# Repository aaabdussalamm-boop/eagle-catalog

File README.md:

# 🔌 Eagle Catalog

Koleksi desain PCB untuk aplikasi **Biomedical, Audio, dan Power Supply** menggunakan Autodesk Eagle.

🌐 **Website:** https://aaabdussalamm-boop.github.io/eagle-catalog/

---

## 📂 Daftar Proyek

### ⚕️ Biomedical Electronics

#### 1. **Holter AD - 2 Channel ECG Monitor**
Holter monitor untuk monitoring ECG jangka panjang dengan ESP32 DevKit V1.
- **IC Utama:** 2x AD620, TL084
- **MCU:** ESP32 DevKit V1
- **Fitur:** Dual channel, WiFi/Bluetooth
- **Files:** [`HOLTER AD.sch`](HOLTER%20AD.sch) | [`HOLTER AD.brd`](HOLTER%20AD.brd)

#### 2. **ECG Circuit**
Rangkaian elektrokardiogram single channel dengan DRL circuit.
- **IC Utama:** AD620, TL084, OP07
- **Fitur:** DRL (Driven Right Leg) circuit
- **Files:** [`ecg.sch`](ecg.sch) | [`ecg.brd`](ecg.brd)

---

### 🎵 Audio Electronics

#### 3. **PCG Quad - Preamp & Filter**
Preamp dan filter audio 4-channel menggunakan TL084 dengan built-in voltage inverter.
- **IC Utama:** TL084 (Quad Op-Amp)
- **Power:** Built-in IC 7660 inverter
- **Supply:** ±12V atau ±15V
- **Files:** [`pcg_quad.sch`](pcg_quad.sch) | [`pcg_quad.brd`](pcg_quad.brd)

---

### ⚡ Power Supply

#### 4. **IC 7660 - Voltage Inverter**
Rangkaian pembuat tegangan negatif untuk dual supply op-amp.
- **IC Utama:** ICL7660
- **Input:** +5V hingga +12V DC
- **Output:** -5V hingga -12V DC
- **Arus Max:** 100mA
- **Files:** [`7660.sch`](7660.sch) | [`7660.brd`](7660.brd)

---

## 🚀 Cara Menggunakan

### 1. **Clone Repository**
```bash
git clone https://github.com/aaabdussalamm-boop/eagle-catalog.git
cd eagle-catalog
```

### 2. **Buka di Eagle**
- Download Autodesk Eagle (versi gratis tersedia)
- Buka file `.sch` untuk melihat schematic
- Buka file `.brd` untuk melihat board layout

### 3. **Edit & Customize**
- Modifikasi sesuai kebutuhan Anda
- Jalankan DRC (Design Rule Check)
- Export ke Gerber untuk produksi PCB

---

## 🤝 Kontribusi

**Kami menerima kontribusi dari siapa saja!** 🎉

Apakah Anda punya desain PCB yang ingin dibagikan? Ikuti langkah mudah ini:

### Quick Start:
1. **Fork** repository ini
2. **Upload** file .sch dan .brd Anda
3. **Create Pull Request**
4. Tunggu review (1-3 hari)

📖 **Panduan Lengkap:** Baca [CONTRIBUTING.md](CONTRIBUTING.md) untuk tutorial detail dengan screenshot.

### Yang Bisa Dikontribusikan:
- ✅ Schematic Eagle (.sch)
- ✅ Board layout Eagle (.brd)
- ✅ Custom libraries (.lbr)
- ✅ Preview/screenshot (.png, .jpg)
- ✅ Dokumentasi

---

## 📁 Struktur Folder

```
eagle-catalog/
├── projects/
│   ├── biomedical/       # Proyek biomedical
│   ├── audio/            # Proyek audio
│   ├── power-supply/     # Power supply
│   ├── iot-embedded/     # IoT & embedded
│   └── others/           # Kategori lainnya
├── libraries/            # Custom libraries
├── index.html            # Website
└── README.md
```

---

## 🛠️ Software yang Digunakan

- **Autodesk Eagle** - PCB design software
  - Download: https://www.autodesk.com/products/eagle/free-download
  - Versi gratis tersedia untuk hobbyist

---

## 📚 Resources

### Tutorial Eagle:
- [Eagle Tutorial - Sparkfun](https://learn.sparkfun.com/tutorials/using-eagle-schematic)
- [Eagle Documentation - Autodesk](https://www.autodesk.com/products/eagle/learn)

### Untuk Biomedical Projects:
- ⚠️ **PENTING:** Rangkaian biomedical dalam repository ini untuk tujuan pembelajaran dan penelitian saja
- Tidak boleh digunakan untuk diagnosis medis tanpa sertifikasi yang sesuai
- Selalu gunakan isolated power supply untuk keamanan pasien

### PCB Manufacturing:
- [JLCPCB](https://jlcpcb.com/)
- [PCBWay](https://www.pcbway.com/)
- [OSH Park](https://oshpark.com/)

---

## 🐛 Melaporkan Issue

Menemukan bug atau ada saran? Silakan buat [Issue](https://github.com/aaabdussalamm-boop/eagle-catalog/issues) dengan detail yang jelas.

---

## 📜 Lisensi

Repository ini dilisensikan di bawah [MIT License](LICENSE) - silakan gunakan, modifikasi, dan distribusikan dengan bebas.

Dengan berkontribusi ke repository ini, Anda setuju kontribusi Anda juga akan dilisensikan di bawah MIT License.

---

## 🌟 Contributors

Terima kasih kepada semua yang telah berkontribusi! ❤️

<!-- ALL-CONTRIBUTORS-LIST:START -->
<!-- Kontributor akan ditambahkan di sini -->
<!-- ALL-CONTRIBUTORS-LIST:END -->

---

## 💬 Kontak

- **GitHub:** [@aaabdussalamm-boop](https://github.com/aaabdussalamm-boop)
- **Website:** https://aaabdussalamm-boop.github.io/eagle-catalog/
- **Issues:** [Create New Issue](https://github.com/aaabdussalamm-boop/eagle-catalog/issues/new)

---

## 🙏 Acknowledgments

- Komunitas elektronika Indonesia
- Autodesk Eagle Community
- Semua kontributor open source

---

**⭐ Jangan lupa beri star jika repository ini bermanfaat!**

Made with ❤️ for the electronics community

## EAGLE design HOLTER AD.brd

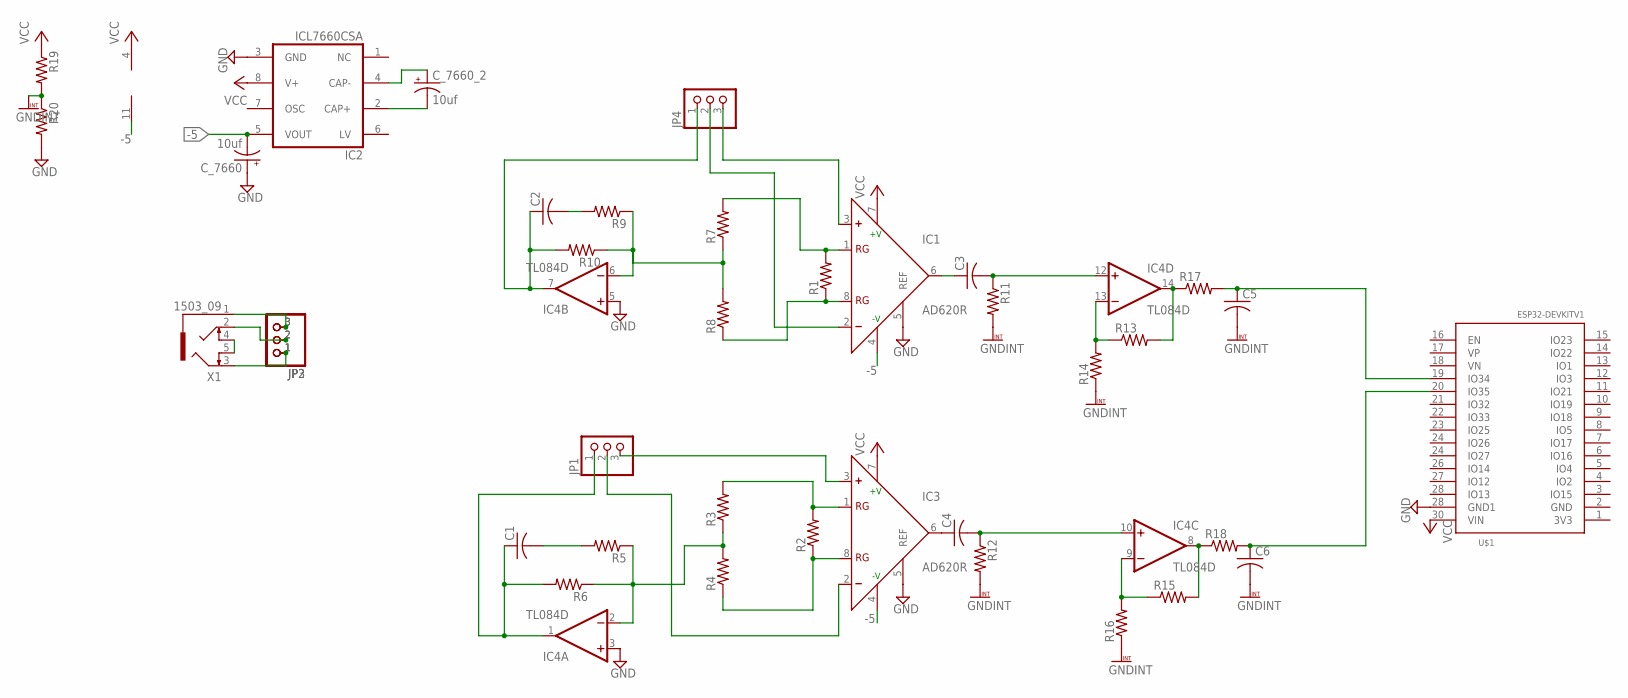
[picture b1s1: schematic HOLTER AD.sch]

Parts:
C1, C2, C3, C4, C5, C6: C-US050-030X075; C050-030X075
C_7660, C_7660_2: 10uf; E2-5
IC1, IC3: AD620R; SO8
IC2: ICL7660CSA; SO08
IC4: TL084D; SO14
JP1, JP2, JP3, JP4: PINHD-1X3; 1X03
R1, R2, R3, R4, R5, R6, R7, R8, R9, R10, R11, R12, R13, R14, R15, R16, R17, R18, R19, R20: R-US_0207/10; 0207/10
U$1: ESP32DEVKITV1; ESP32-DEVKITV1
X1: 1503_09

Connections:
-5: C_7660.-, IC1.4 (-V), IC2.5 (VOUT), IC3.4 (-V), IC4.11 (V-)
GND: C_7660.+, IC1.5 (REF), IC2.3 (GND), IC3.5 (REF), IC4.3 (+IN), IC4.5 (+IN), R20.2, U$1.28 (IO13)
GNDINT: C5.2, C6.2, R11.2, R12.2, R14.1, R16.1, R19.2, R20.1
unnamed: X1.4, X1.5
unnamed: C_7660_2.+, IC2.4 (CAP-)
unnamed: IC1.1 (RG), R1.2, R7.2
unnamed: IC1.8 (RG), R1.1, R8.1
unnamed: IC3.1 (RG), R2.2, R3.2
unnamed: C_7660_2.-, IC2.2 (CAP+)
unnamed: IC3.8 (RG), R2.1, R4.1
unnamed: IC1.3 (+), JP4.3
unnamed: IC1.2 (-), JP4.2
unnamed: IC4.2 (-IN), R3.1, R4.2, R5.1, R6.1
unnamed: C2.2, R9.2
unnamed: C1.2, R5.2
unnamed: C1.1, IC4.1 (OUT), JP1.1, R6.2
unnamed: IC3.3 (+), JP1.3
unnamed: IC4.6 (-IN), R7.1, R8.2, R9.1, R10.1
unnamed: C2.1, IC4.7 (OUT), JP4.1, R10.2
unnamed: JP2.1, JP3.1, X1.3
unnamed: JP2.2, JP3.2, X1.2
unnamed: JP2.3, JP3.3, X1.1
unnamed: C3.2, IC4.12 (+IN), R11.1
unnamed: C3.1, IC1.6 (OUT)
unnamed: IC3.2 (-), JP1.2
unnamed: C4.1, IC3.6 (OUT)
unnamed: C4.2, IC4.10 (+IN), R12.1
unnamed: IC4.13 (-IN), R13.1, R14.2
unnamed: IC4.14 (OUT), R13.2, R17.1
unnamed: IC4.9 (-IN), R15.1, R16.2
unnamed: IC4.8 (OUT), R15.2, R18.1
unnamed: C6.1, R18.2, U$1.20 (IO35)
unnamed: C5.1, R17.2, U$1.19 (IO34)
VCC: IC1.7 (+V), IC2.8 (V+), IC3.7 (+V), IC4.4 (V+), R19.1, U$1.30 (VIN)

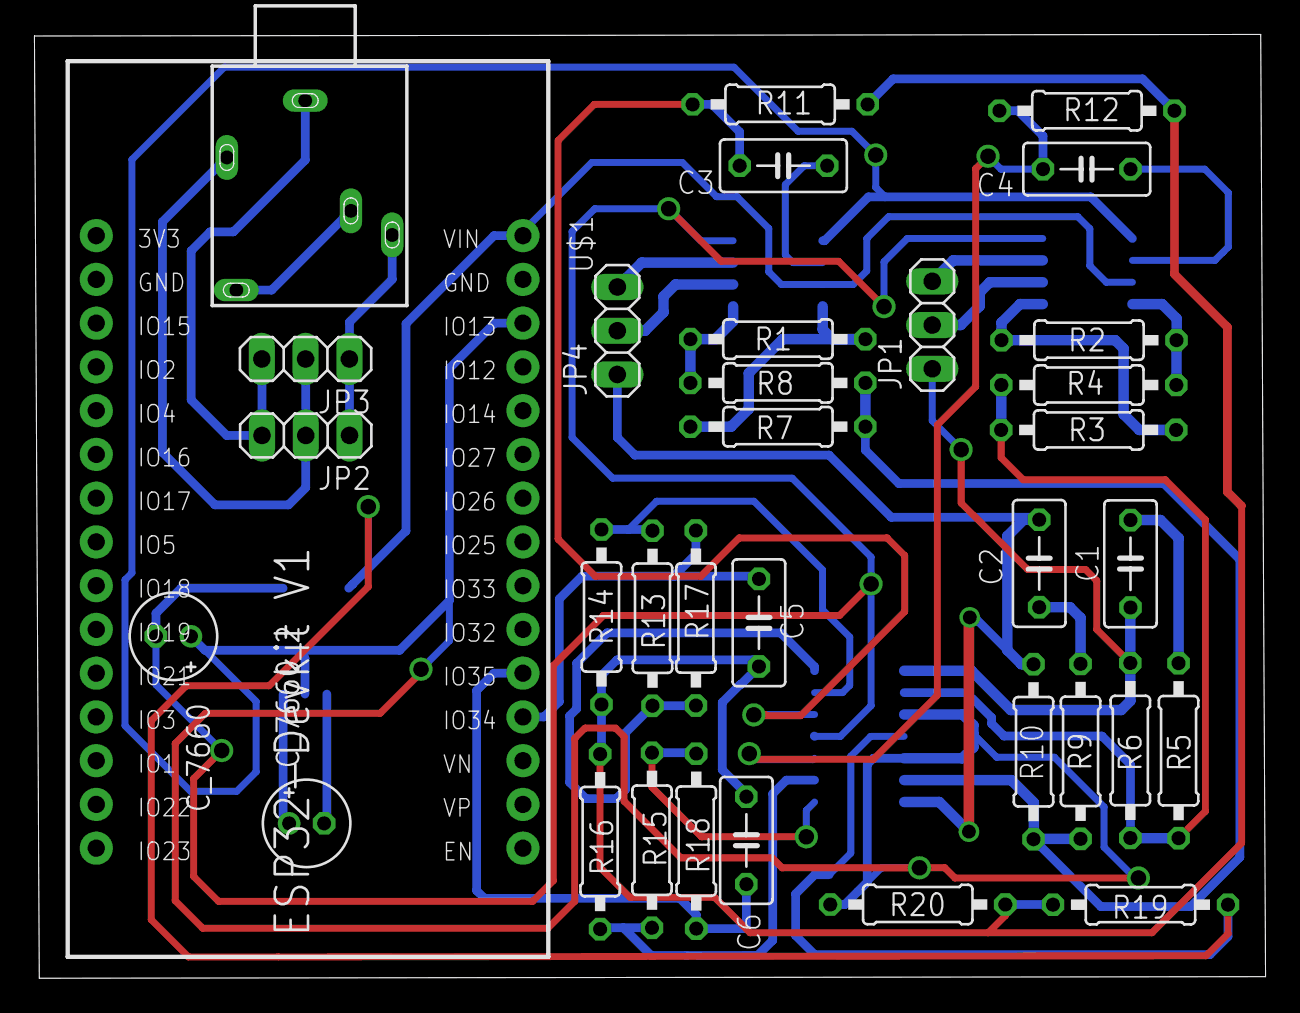
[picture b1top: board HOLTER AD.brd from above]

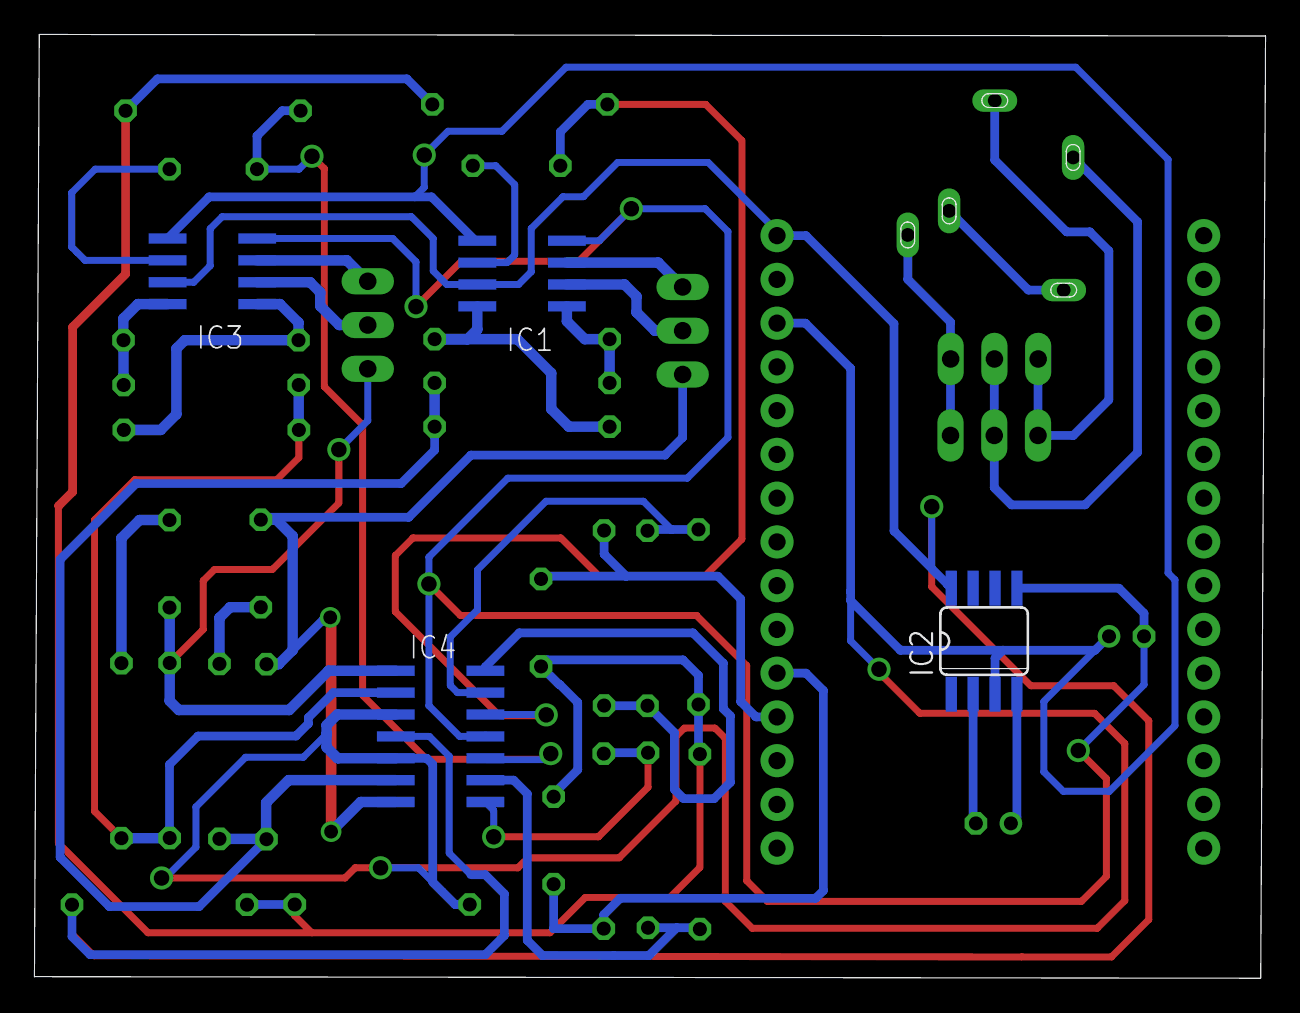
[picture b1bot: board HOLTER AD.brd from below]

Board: 2 copper layers, 71.5 x 54.8 mm, 38 parts (4 on the bottom side), 34 nets.

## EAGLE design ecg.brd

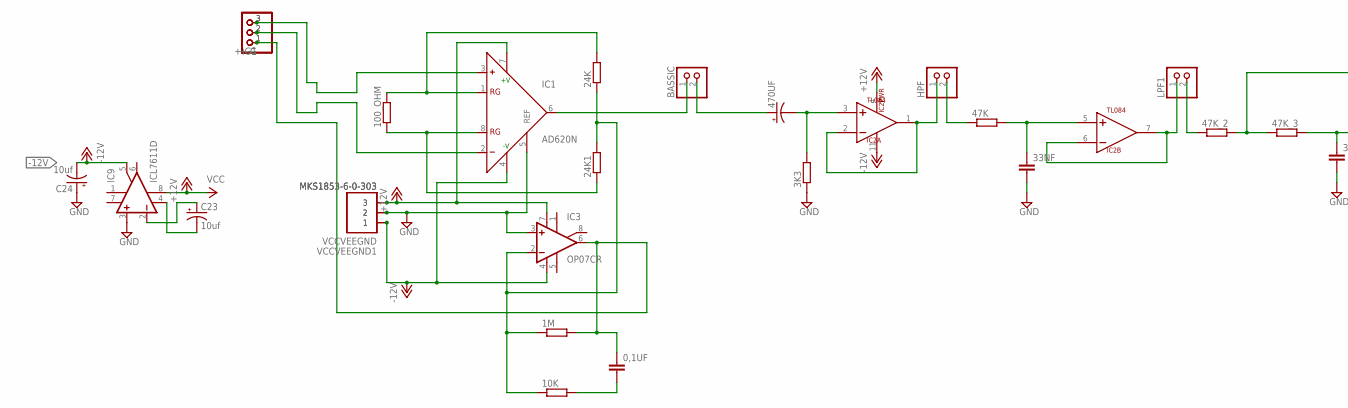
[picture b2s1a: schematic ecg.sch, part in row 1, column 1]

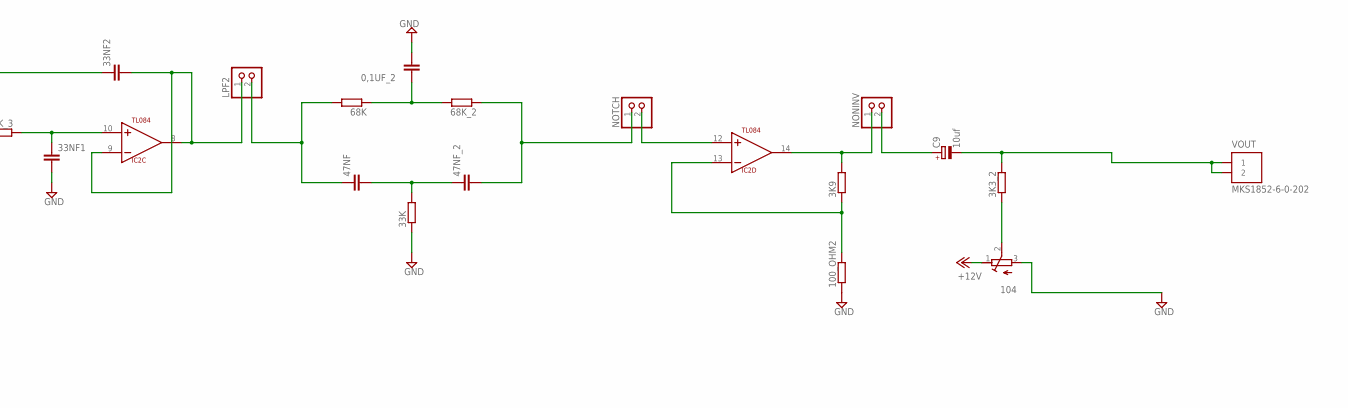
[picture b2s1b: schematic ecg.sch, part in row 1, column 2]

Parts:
0,1UF, 0,1UF_2, 33NF, 33NF1, 33NF2, 47NF, 47NF_2: C-EUC1206; C1206
1M, 3K3_2, 3K9, 33K, 47K_2, 47K_3, 68K, 68K_2, 100_OHM2: R-EU_R1206; R1206
3K3, 10K, 24K, 24K1, 47K, 100_OHM: R-EU_M1206; M1206
104: R-TRIMMT93YA; RTRIMT93YA
470UF: CPOL-US140CLH-1010; 140CLH-1010
+-G, +-G1: PINHD-1X3; 1X03
BASSIC: PINHD-1X2; 1X02
C9: 10uf; 140CLH-0810
C23, C24: 10uf; 150CLZ-0810
HPF: PINHD-1X2; 1X02
IC1: AD620N; DIL08
IC2: TL084; SO14
IC3: OP07CR; SO08
IC9: ICL7611D; SO08
LPF1, LPF2: PINHD-1X2; 1X02
NONINV: PINHD-1X2; 1X02
NOTCH: PINHD-1X2; 1X02
VCCVEEGND, VCCVEEGND1: MKS1853-6-0-303
VOUT: MKS1852-6-0-202

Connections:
+12V: 104.1 (E), IC1.7 (+V), IC2.4 (VCC+), IC3.7 (V+), IC9.8 (OPT), VCCVEEGND.3, VCCVEEGND1.3
-12V: C24.-, IC1.4 (-V), IC2.11 (VCC-), IC3.4 (V-), IC9.5 (ON2), VCCVEEGND.1, VCCVEEGND1.1
GND: 0,1UF_2.2, 3K3.1, 33K.1, 33NF.2, 33NF1.2, 100_OHM2.1, 104.3 (A), C24.+, IC1.5 (REF), IC3.3 (+IN), IC9.3 (+IN), VCCVEEGND.2, VCCVEEGND1.2
unnamed: 0,1UF.1, 1M.2, +-G.1, +-G1.1, IC3.6 (OUT)
unnamed: 0,1UF.2, 10K.2
unnamed: 24K1.1, 100_OHM.1, IC1.8 (RG)
unnamed: 24K.2, 100_OHM.2, IC1.1 (RG)
unnamed: 1M.1, 10K.1, 24K.1, 24K1.2, IC3.2 (-IN)
unnamed: 470UF.+, BASSIC.2
unnamed: 3K3.2, 470UF.-, IC2.3 (IN+)
unnamed: +-G.2, +-G1.2, IC1.2 (-)
unnamed: +-G.3, +-G1.3, IC1.3 (+)
unnamed: BASSIC.1, IC1.6 (OUT)
unnamed: HPF.1, IC2.1 (OUT), IC2.2 (IN-)
unnamed: 33NF.1, 47K.2, IC2.5 (IN+)
unnamed: IC2.6 (IN-), IC2.7 (OUT), LPF1.1
unnamed: 33NF2.1, 47K_2.2, 47K_3.1
unnamed: 33NF1.1, 47K_3.2, IC2.10 (IN+)
unnamed: 33NF2.2, IC2.8 (OUT), IC2.9 (IN-), LPF2.1
unnamed: 3K9.2, IC2.14 (OUT), NONINV.1
unnamed: 47NF.1, 68K.2, LPF2.2
unnamed: 0,1UF_2.1, 68K.1, 68K_2.2
unnamed: 33K.2, 47NF.2, 47NF_2.1
unnamed: 47NF_2.2, 68K_2.1, NOTCH.1
unnamed: 47K.1, HPF.2
unnamed: 47K_2.1, LPF1.2
unnamed: 3K9.1, 100_OHM2.2, IC2.13 (IN-)
unnamed: C9.+, NONINV.2
unnamed: 3K3_2.1, 104.2 (S)
unnamed: IC2.12 (IN+), NOTCH.2
unnamed: 3K3_2.2, C9.-, VOUT.1, VOUT.2
unnamed: C23.+, IC9.2 (-IN)
unnamed: C23.-, IC9.4 (V-)
V+: IC9.7 (V+)

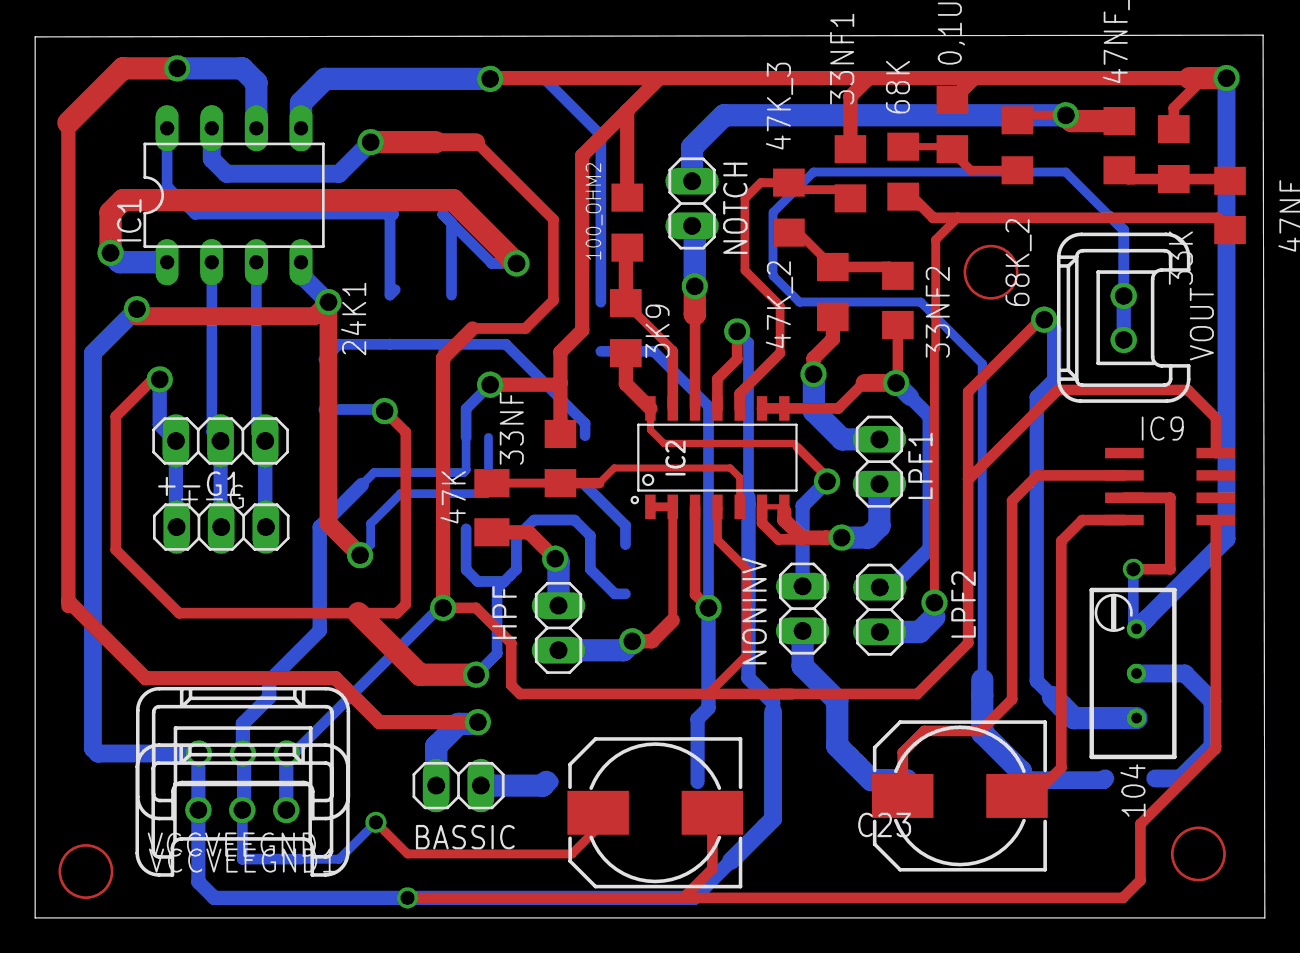
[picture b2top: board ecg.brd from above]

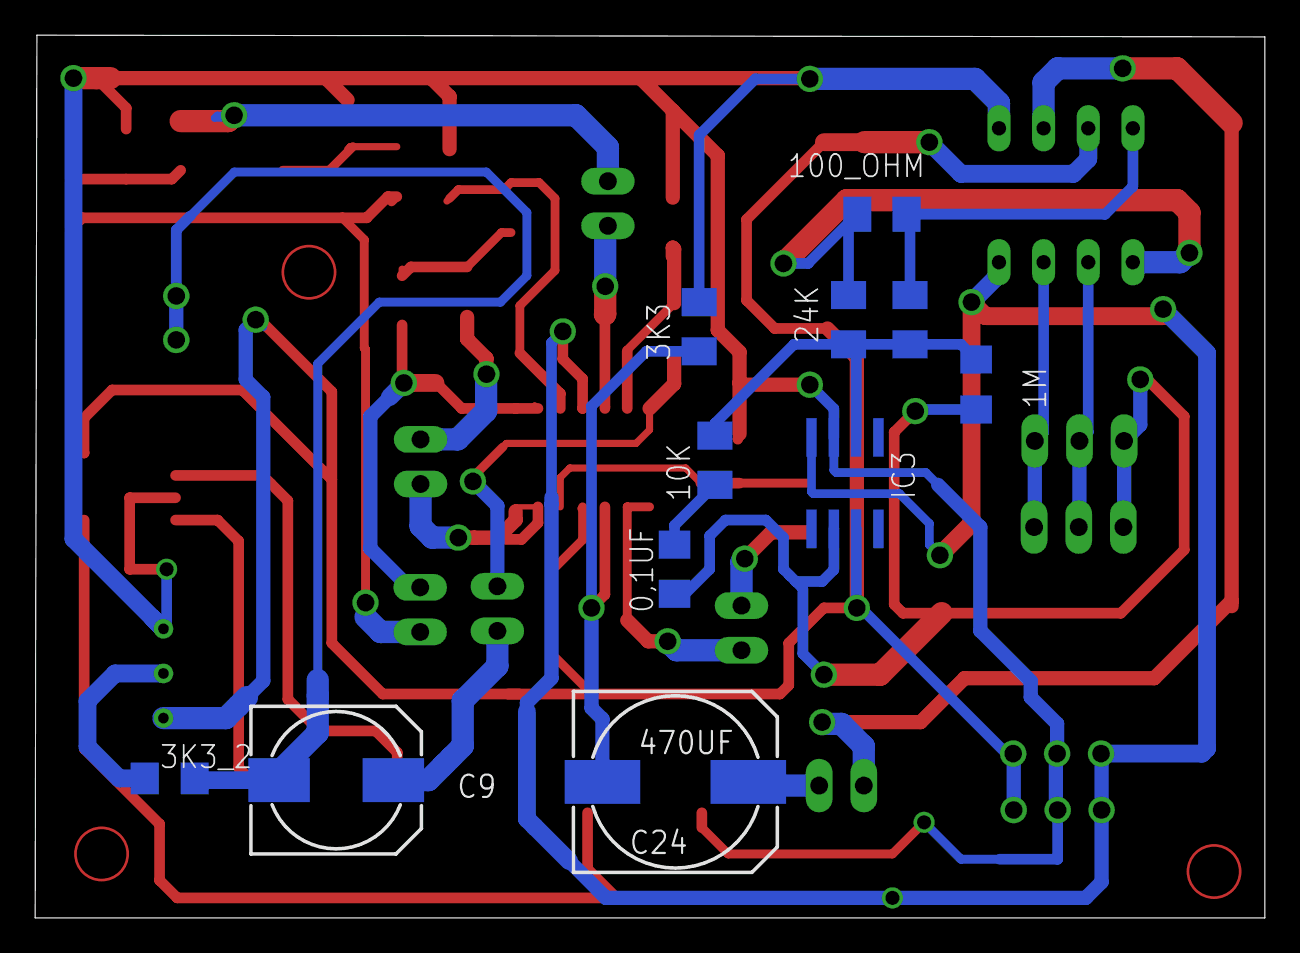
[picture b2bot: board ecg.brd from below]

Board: 2 copper layers, 70.0 x 50.2 mm, 42 parts (11 on the bottom side), 33 nets.

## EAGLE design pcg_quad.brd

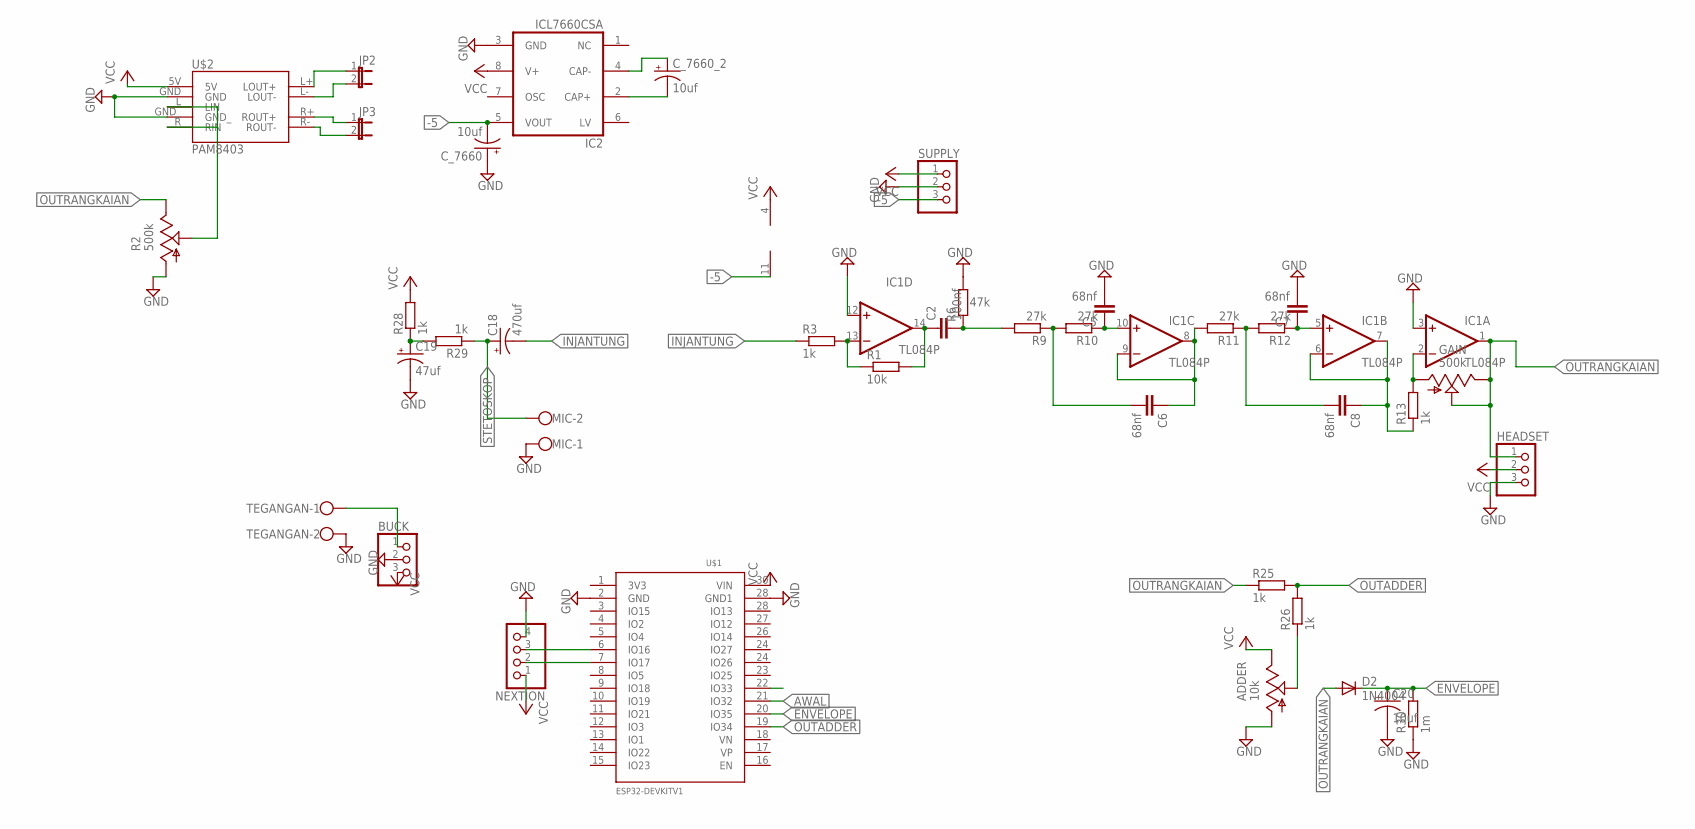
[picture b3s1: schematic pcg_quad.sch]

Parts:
ADDER: 10k; B64Y
BUCK: PINHD-1X3; 1X03
C2: 100nf; C050-025X075
C5, C6, C7, C8: 68nf; C050-025X075
C18: 470uf; E2,5-7
C19: 47uf; E2-5
C20: 10uf; E2-5
C_7660, C_7660_2: 10uf; E2-5
D2: 1N4004; DO41-10
GAIN: 500k; B64Y
HEADSET: PINHD-1X3; 1X03
IC1: TL084P; DIL14
IC2: ICL7660CSA; SO08
JP2, JP3: JP1E; JP1
MIC: W237-102
NEXTION: PINHD-1X4; 1X04
R1: 10k; 0309/10
R2: 500k; B64Y
R3, R13, R25, R26, R28, R29: 1k; 0309/10
R6: 47k; 0309/10
R9, R10, R11, R12: 27k; 0309/10
R30: 1m; 0309/10
SUPPLY: PINHD-1X3; 1X03
TEGANGAN: W237-102
U$1: ESP32DEVKITV1; ESP32-DEVKITV1
U$2: PAM8403

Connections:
-5: C_7660.-, IC1.11 (V-), IC2.5 (VOUT), SUPPLY.3
AWAL: U$1.21 (IO32)
ENVELOPE: C20.+, D2.C, R30.2, U$1.20 (IO35)
GND: ADDER.A, BUCK.2, C5.2, C7.2, C19.-, C20.-, C_7660.+, HEADSET.3, IC1.3 (+IN), IC1.12 (+IN), IC2.3 (GND), MIC.1, NEXTION.4, R2.A, R6.2, R30.1, SUPPLY.2, TEGANGAN.2, U$1.2 (GND), U$1.28 (IO13), U$2.GND, U$2.GND_
INJANTUNG: C18.-, R3.1
unnamed: IC1.13 (-IN), R1.1, R3.2
unnamed: C_7660_2.+, IC2.4 (CAP-)
unnamed: BUCK.1, TEGANGAN.1
unnamed: R2.S, U$2.L (LIN), U$2.R (RIN)
unnamed: JP2.1, U$2.L+ (LOUT+)
unnamed: C_7660_2.-, IC2.2 (CAP+)
unnamed: C2.2, R6.1, R9.2
unnamed: NEXTION.3, U$1.6 (IO16)
unnamed: NEXTION.2, U$1.7 (IO17)
unnamed: JP2.2, U$2.L- (LOUT-)
unnamed: JP3.1, U$2.R+ (ROUT+)
unnamed: C6.2, R9.1, R10.2
unnamed: C5.1, IC1.10 (+IN), R10.1
unnamed: C6.1, IC1.8 (OUT), IC1.9 (-IN), R11.2
unnamed: C8.2, R11.1, R12.2
unnamed: C7.1, IC1.5 (+IN), R12.1
unnamed: C8.1, IC1.6 (-IN), IC1.7 (OUT), R13.1
unnamed: GAIN.A, IC1.2 (-IN), R13.2
unnamed: JP3.2, U$2.R- (ROUT-)
unnamed: ADDER.S, R26.1
unnamed: C19.+, R28.1, R29.2
OUTADDER: R25.2, R26.2, U$1.19 (IO34)
OUTRANGKAIAN: D2.A, GAIN.E, GAIN.S, HEADSET.1, IC1.1 (OUT), R2.E, R25.1
STETOSKOP: C18.+, MIC.2, R29.1
TEST: C2.1, IC1.14 (OUT), R1.2
VCC: ADDER.E, BUCK.3, HEADSET.2, IC1.4 (V+), IC2.8 (V+), NEXTION.1, R28.2, SUPPLY.1, U$1.30 (VIN), U$2.5V

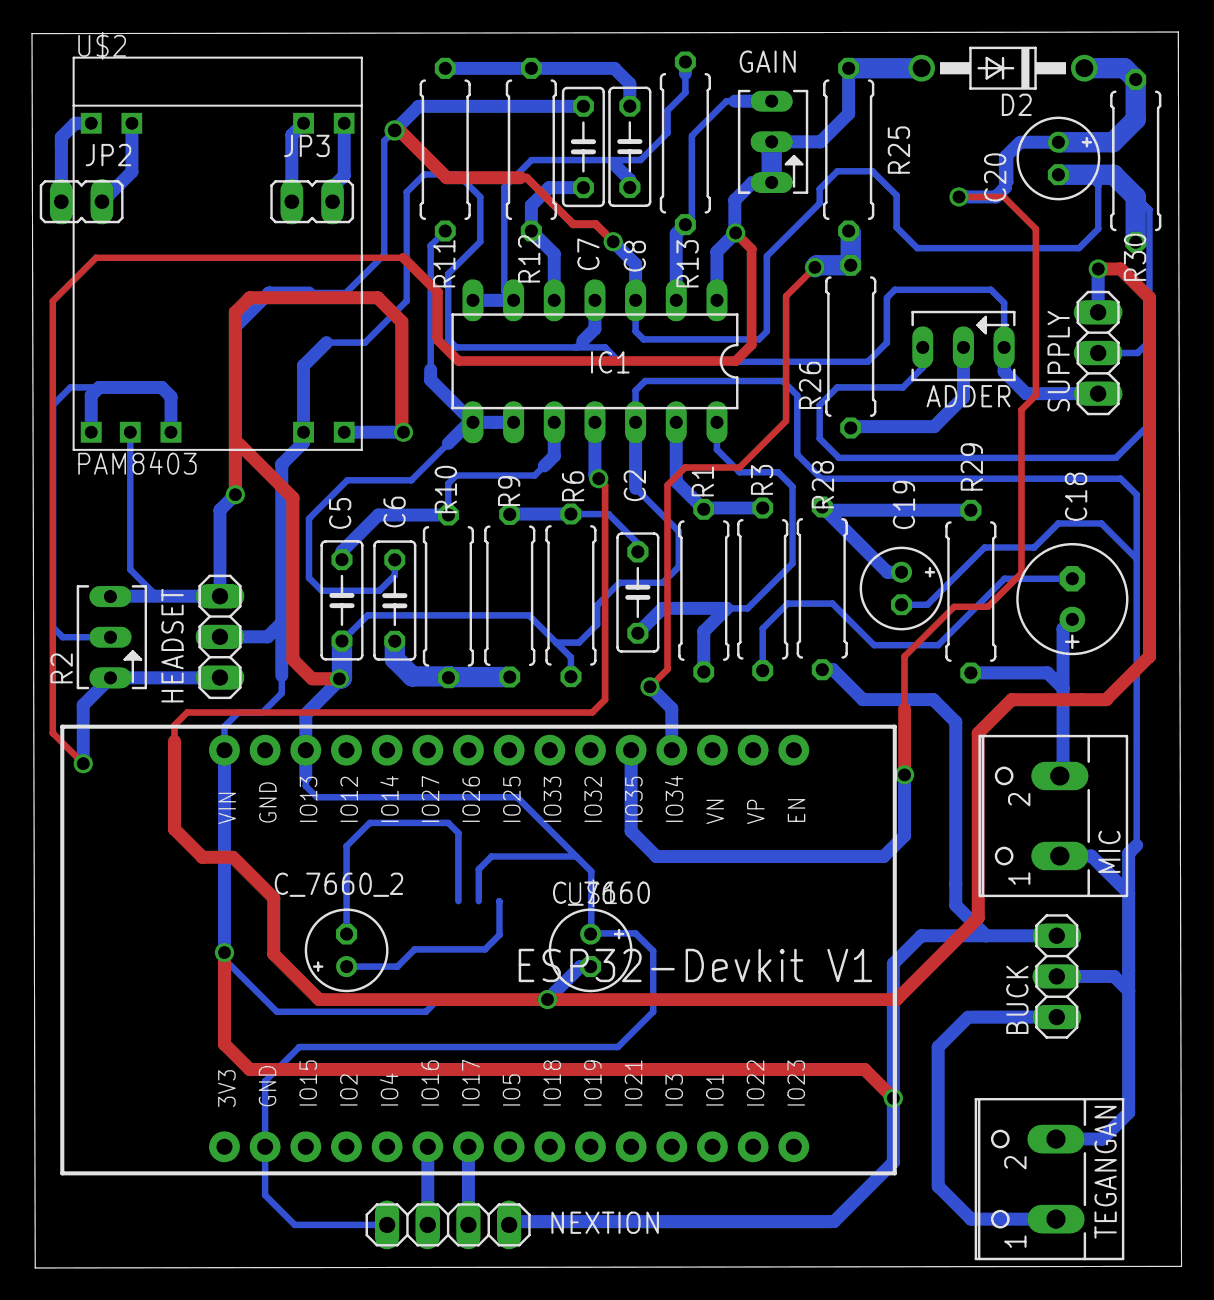
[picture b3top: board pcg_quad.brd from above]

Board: 2 copper layers, 71.8 x 77.2 mm, 39 parts (1 on the bottom side), 30 nets.

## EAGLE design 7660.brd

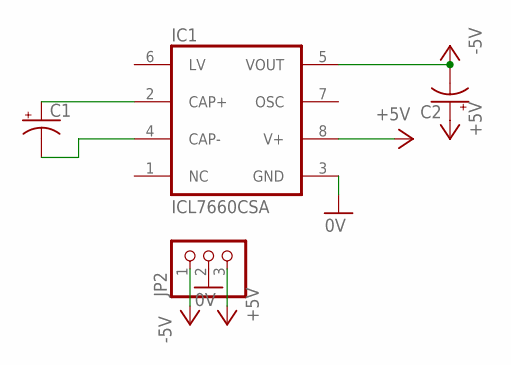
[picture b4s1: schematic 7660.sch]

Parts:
C1, C2: CPOL-USE2,5-6E; E2,5-6E
IC1: ICL7660CSA; SO08
JP2: PINHD-1X3; 1X03

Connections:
0V: IC1.3 (GND), JP2.2
+5V: C2.+, IC1.8 (V+), JP2.3
-5V: C2.-, IC1.5 (VOUT), JP2.1
unnamed: C1.+, IC1.2 (CAP+)
unnamed: C1.-, IC1.4 (CAP-)

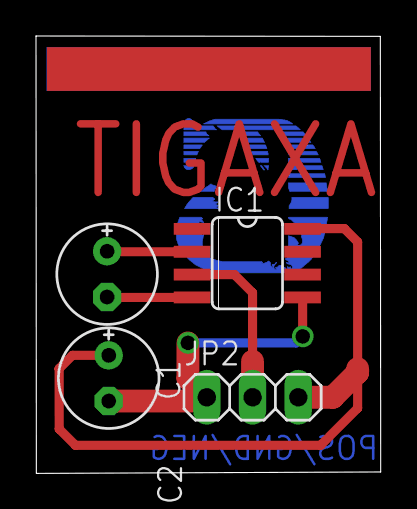
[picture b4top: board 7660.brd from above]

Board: 2 copper layers, 19.2 x 24.3 mm, 5 parts (1 on the bottom side), 5 nets.

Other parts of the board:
U$1: CS-LOGO-TOP-8MM

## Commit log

2026-01-21 tampilan web pertama
    This HTML file contains a collection of PCB designs created with Autodesk Eagle, including a header, project cards, and usage instructions.
2026-01-21 menambahkan file rangkaian 7660
    Updated the title and header text to reflect the new catalog name. Enhanced project descriptions and added download links for schematic and board files.
2026-01-21 penambahan rangkaian pcg
    Updated project descriptions and specifications for clarity. Added a new badge style for projects.
2026-01-21 menambahkan rangkaian ecg
2026-01-22 Add contribution guidelines to CONTRIBUTING.md
    Added a comprehensive contribution guide for the Eagle Catalog project, detailing what can be contributed, how to contribute via GitHub, folder structure, pull request templates, and quality tips.
2026-01-22 Enhance README with project details and guidelines
    Added detailed project descriptions, usage instructions, and contribution guidelines to the README.
2026-01-22 Add contribution section and update footer
2026-01-22 Add pull request template for project submissions

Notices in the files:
README.md:
License: MIT
